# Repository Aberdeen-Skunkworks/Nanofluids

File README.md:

# Nanofluids

Project background:

Moore's Law is a well-known phenomenon that states that in highly dense integrated circuits (IC) the total number of transistors will approximately double every two years. Thermal management becomes unrealistic as the density of transistors with in the IC increase, thus a new challenge has appeared in heat transfer: cooling of nano-scale devices. A more efficient and compact design of heat exchangers is required for advanced nanoelectronics, and one way this can be achieved is through nanofluid technology. A very large enhancement of the thermal conductivity of a base fluid (i.e. water) can be achieved by the addition of highly conductive solid material in the form of nanoparticles. The mechanics of this enhancement have generally fallen into the classical/continuum bounds given by series and parallel resistances. These bounds are defined by two separate phases of the solid nanoparticles and the liquid medium and the arrangement of the nanoparticles with in the medium. But a small number of experimental result do not fall into these bounds such as helium and hydrogen gas mixtures or the theoretical hard sphere model, which instead exhibit conductivity enhancements above the parallel bounds and dehancement below the series bounds. This project is to explore this phenomena, both experimentally and theoretically, and to attempt to model its effects.

Project Objectives

• Review nanofluids and their history in thermal conductivity enhancement. This includes describing what models have already been used to approximate their behaviour and critically review their applicability.

•	Construct a Transient Heated Wire cell for the testing of liquid and gas mixture thermal conductivities and use this data to explore the anomalous heat transfer in nanofluids and gas mixtures which have similar dimensional properties to nanofluid systems.

• Perform molecular simulations of thermal conduction to confirm if transient effects in the thermal conductivity, possible at small time/length scales, dominate conduction. These simulations may be molecular dynamics simulations using DynamO, or coupled kinetic theory-hydrodynamics simulations using code developed by Craig Moir, a PhD student at Aberdeen

•	Explore new heat exchanger designs which incorporate any time-dependent anomalous phenomena

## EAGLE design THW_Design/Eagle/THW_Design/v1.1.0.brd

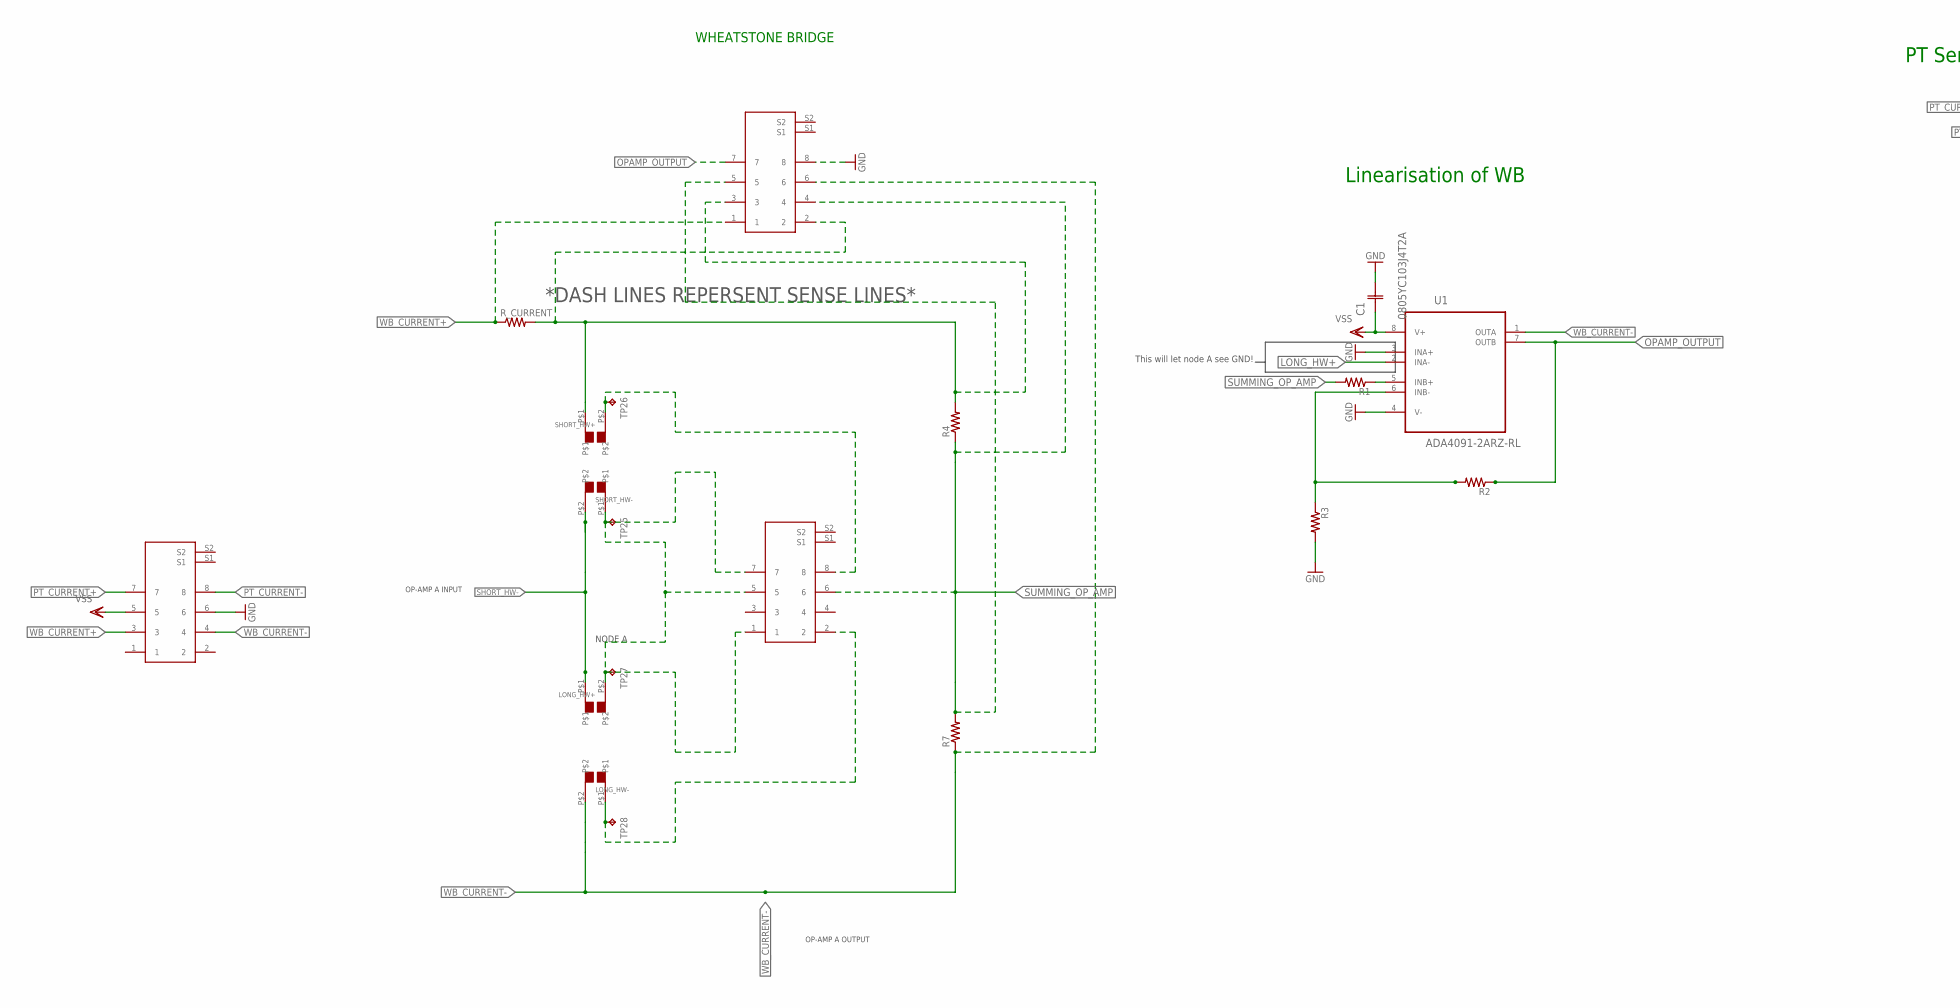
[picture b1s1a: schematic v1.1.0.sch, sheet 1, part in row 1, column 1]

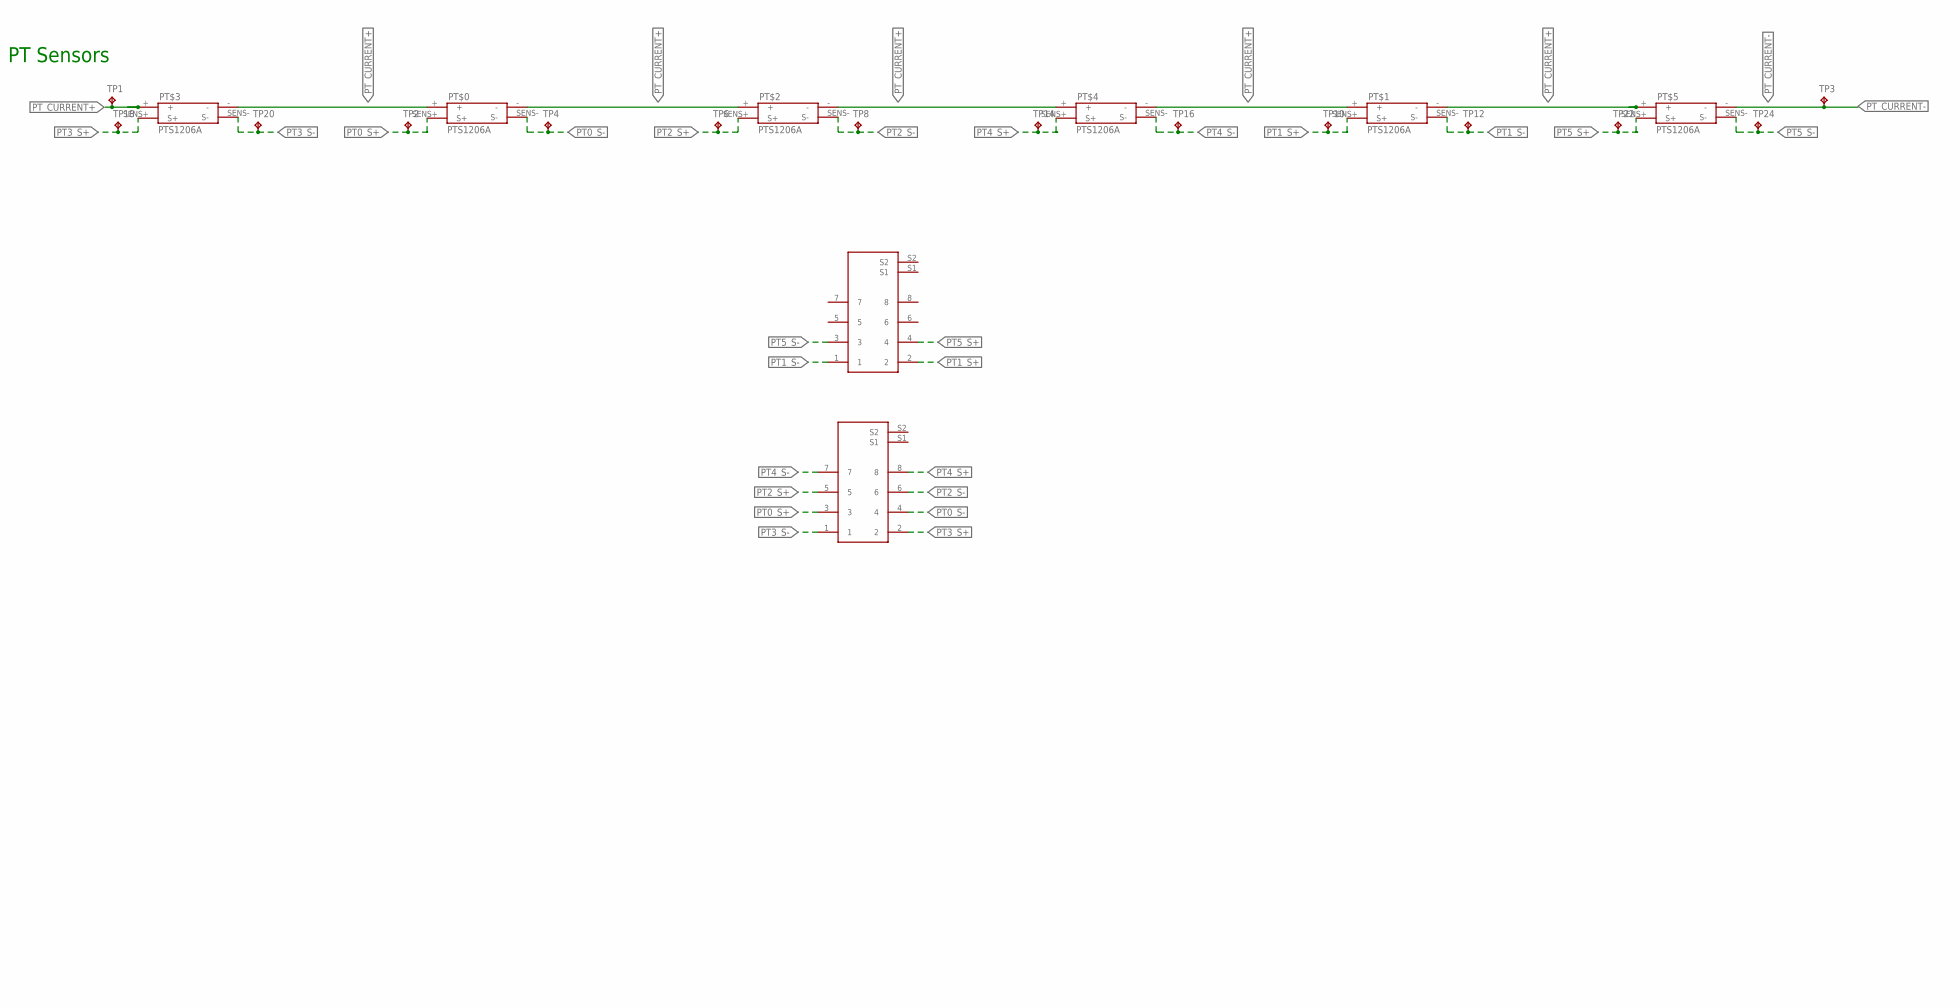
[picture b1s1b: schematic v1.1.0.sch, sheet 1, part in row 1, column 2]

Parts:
C1: 0805YC103J4T2A; CAPC2012X94N
LONG_HW+: WIREPOINT_1A; WIREPOINT
LONG_HW-: WIREPOINT_1A; WIREPOINT
POWER: RJ45_CONNECTOR; RJ45_CONNNECTOR
PT$0, PT$1, PT$2, PT$3, PT$4, PT$5: PTS1206A; CAPMP3216X166
PT_SENS1, PT_SENS2: RJ45_CONNECTOR; RJ45_CONNNECTOR
R1, R2, R3, R4, R7: R-US_M0805; M0805
R_CURRENT: R-US_M0805; M0805
SHORT_HW+: WIREPOINT_1A; WIREPOINT
SHORT_HW-: WIREPOINT_1A; WIREPOINT
TP1, TP2, TP3, TP4, TP6, TP8, TP10, TP12, TP14, TP16, TP18, TP20, TP22, TP24, TP25, TP26, TP27, TP28: TPTP10SQ; TP10SQ
U1: ADA4091-2ARZ-RL; SOIC127P600X175-8N
WB_SENS1, WB_SENS2: RJ45_CONNECTOR; RJ45_CONNNECTOR

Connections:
GND: C1.2 (C2), POWER.6, R3.2, U1.3 (INA+), U1.4 (V-), WB_SENS2.8
LONG_HW+: U1.2 (INA-)
LONG_HW_SENS-: LONG_HW-.P$1, TP28.TP, WB_SENS1.2
unnamed: R1.1, U1.5 (INB+)
unnamed: R2.2, R3.1, U1.6 (INB-)
OPAMP_OUTPUT: R2.1, U1.7 (OUTB), WB_SENS2.7
PT0_S+: PT$0.SENS+ (S+), PT_SENS2.3, TP2.TP
PT0_S-: PT$0.SENS- (S-), PT_SENS2.4, TP4.TP
PT1_S+: PT$1.SENS+ (S+), PT_SENS1.2, TP10.TP
PT1_S-: PT$1.SENS- (S-), PT_SENS1.1, TP12.TP
PT2_S+: PT$2.SENS+ (S+), PT_SENS2.5, TP6.TP
PT2_S-: PT$2.SENS- (S-), PT_SENS2.6, TP8.TP
PT3_S+: PT$3.SENS+ (S+), PT_SENS2.2, TP18.TP
PT3_S-: PT$3.SENS- (S-), PT_SENS2.1, TP20.TP
PT4_S+: PT$4.SENS+ (S+), PT_SENS2.8, TP14.TP
PT4_S-: PT$4.SENS- (S-), PT_SENS2.7, TP16.TP
PT5_S+: PT$5.SENS+ (S+), PT_SENS1.4, TP22.TP
PT5_S-: PT$5.SENS- (S-), PT_SENS1.3, TP24.TP
PT_CURRENT+: POWER.7, PT$0.+, PT$0.-, PT$1.+, PT$1.-, PT$2.+, PT$2.-, PT$3.+, PT$3.-, PT$4.+, PT$4.-, PT$5.+, TP1.TP
PT_CURRENT-: POWER.8, PT$5.-, TP3.TP
SHORT_HW+: R4.2, R_CURRENT.2, SHORT_HW+.P$1, WB_SENS2.2, WB_SENS2.3
SHORT_HW-: LONG_HW+.P$1, SHORT_HW-.P$2
SHORT_HW_SENS+: SHORT_HW+.P$2, TP26.TP, WB_SENS1.8
SHORT_HW_SENS-: LONG_HW+.P$2, SHORT_HW-.P$1, TP25.TP, TP27.TP, WB_SENS1.1, WB_SENS1.5, WB_SENS1.7
SUMMING_OP_AMP: R1.2, R4.1, R7.2, WB_SENS1.6, WB_SENS2.4, WB_SENS2.5
VSS: C1.1 (C1), POWER.5, U1.8 (V+)
WB_CURRENT+: POWER.3, R_CURRENT.1, WB_SENS2.1
WB_CURRENT-: LONG_HW-.P$2, POWER.4, R7.1, U1.1 (OUTA), WB_SENS2.6

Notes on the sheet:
WHEATSTONE BRIDGE
Linearisation of WB
PT Sensors
OP-AMP A INPUT
OP-AMP A OUTPUT
NODE A
This will let node A see GND!
*DASH LINES REPERSENT SENSE LINES*

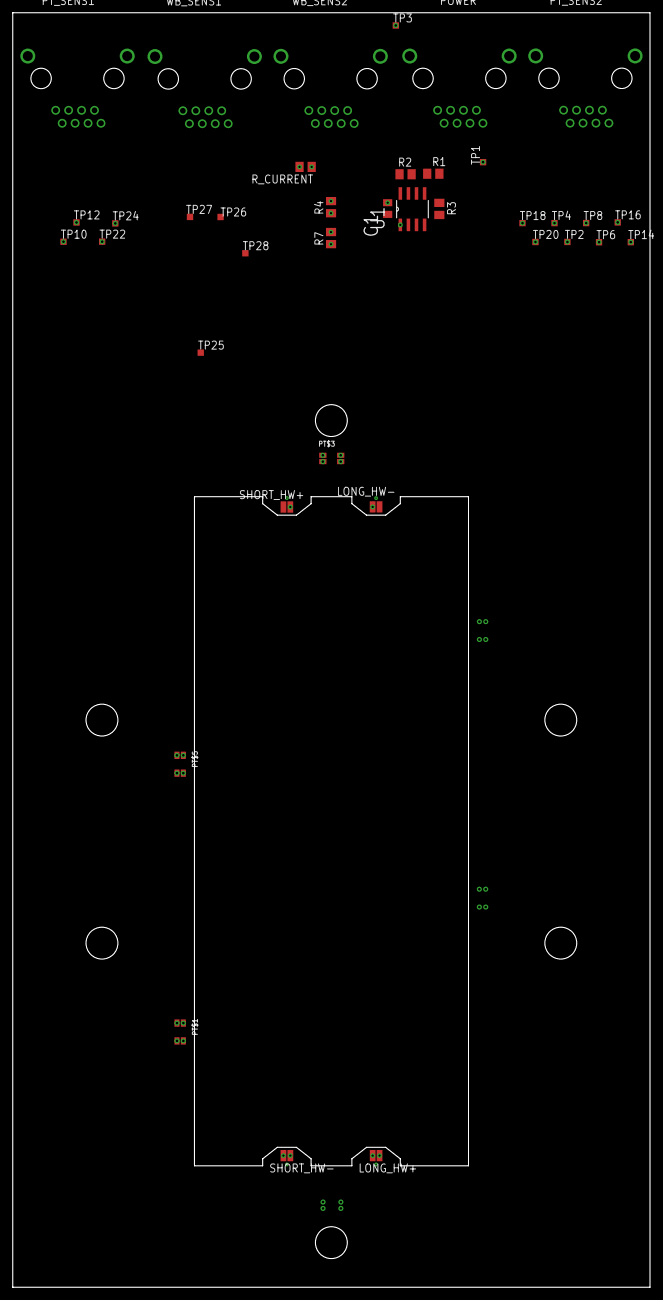
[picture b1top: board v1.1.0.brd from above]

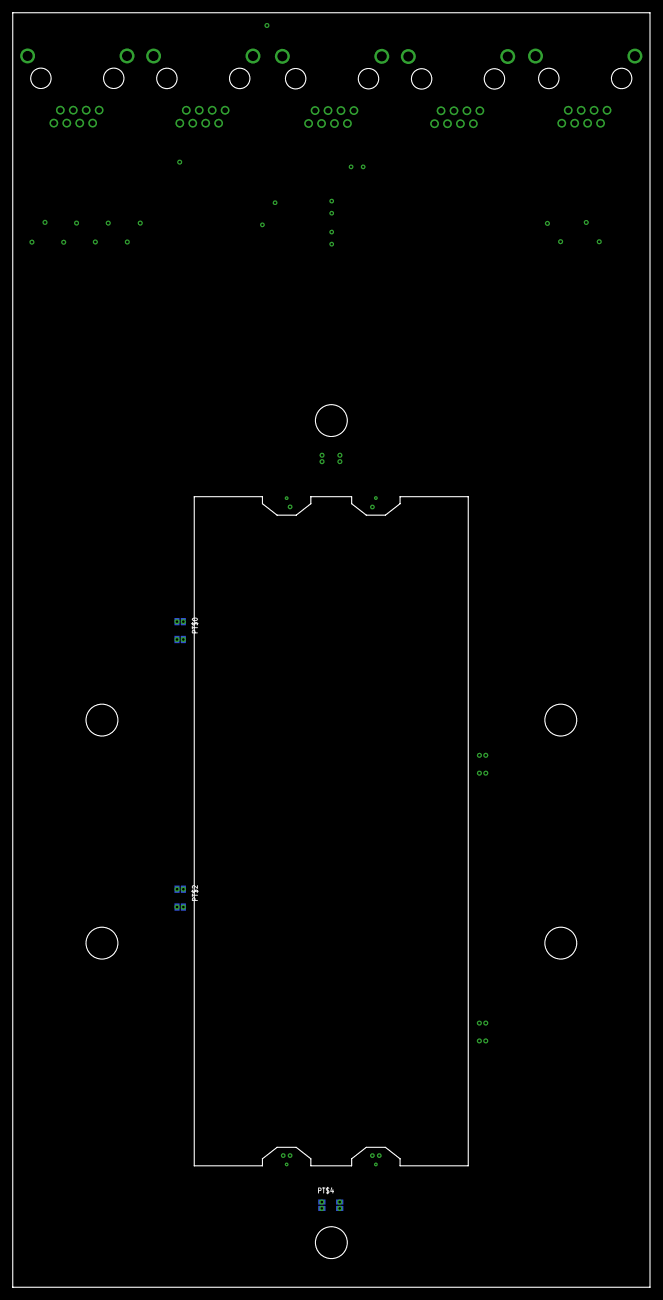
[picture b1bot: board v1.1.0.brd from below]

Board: 4 copper layers, 100.0 x 200.0 mm, 41 parts (3 on the bottom side), 27 nets.

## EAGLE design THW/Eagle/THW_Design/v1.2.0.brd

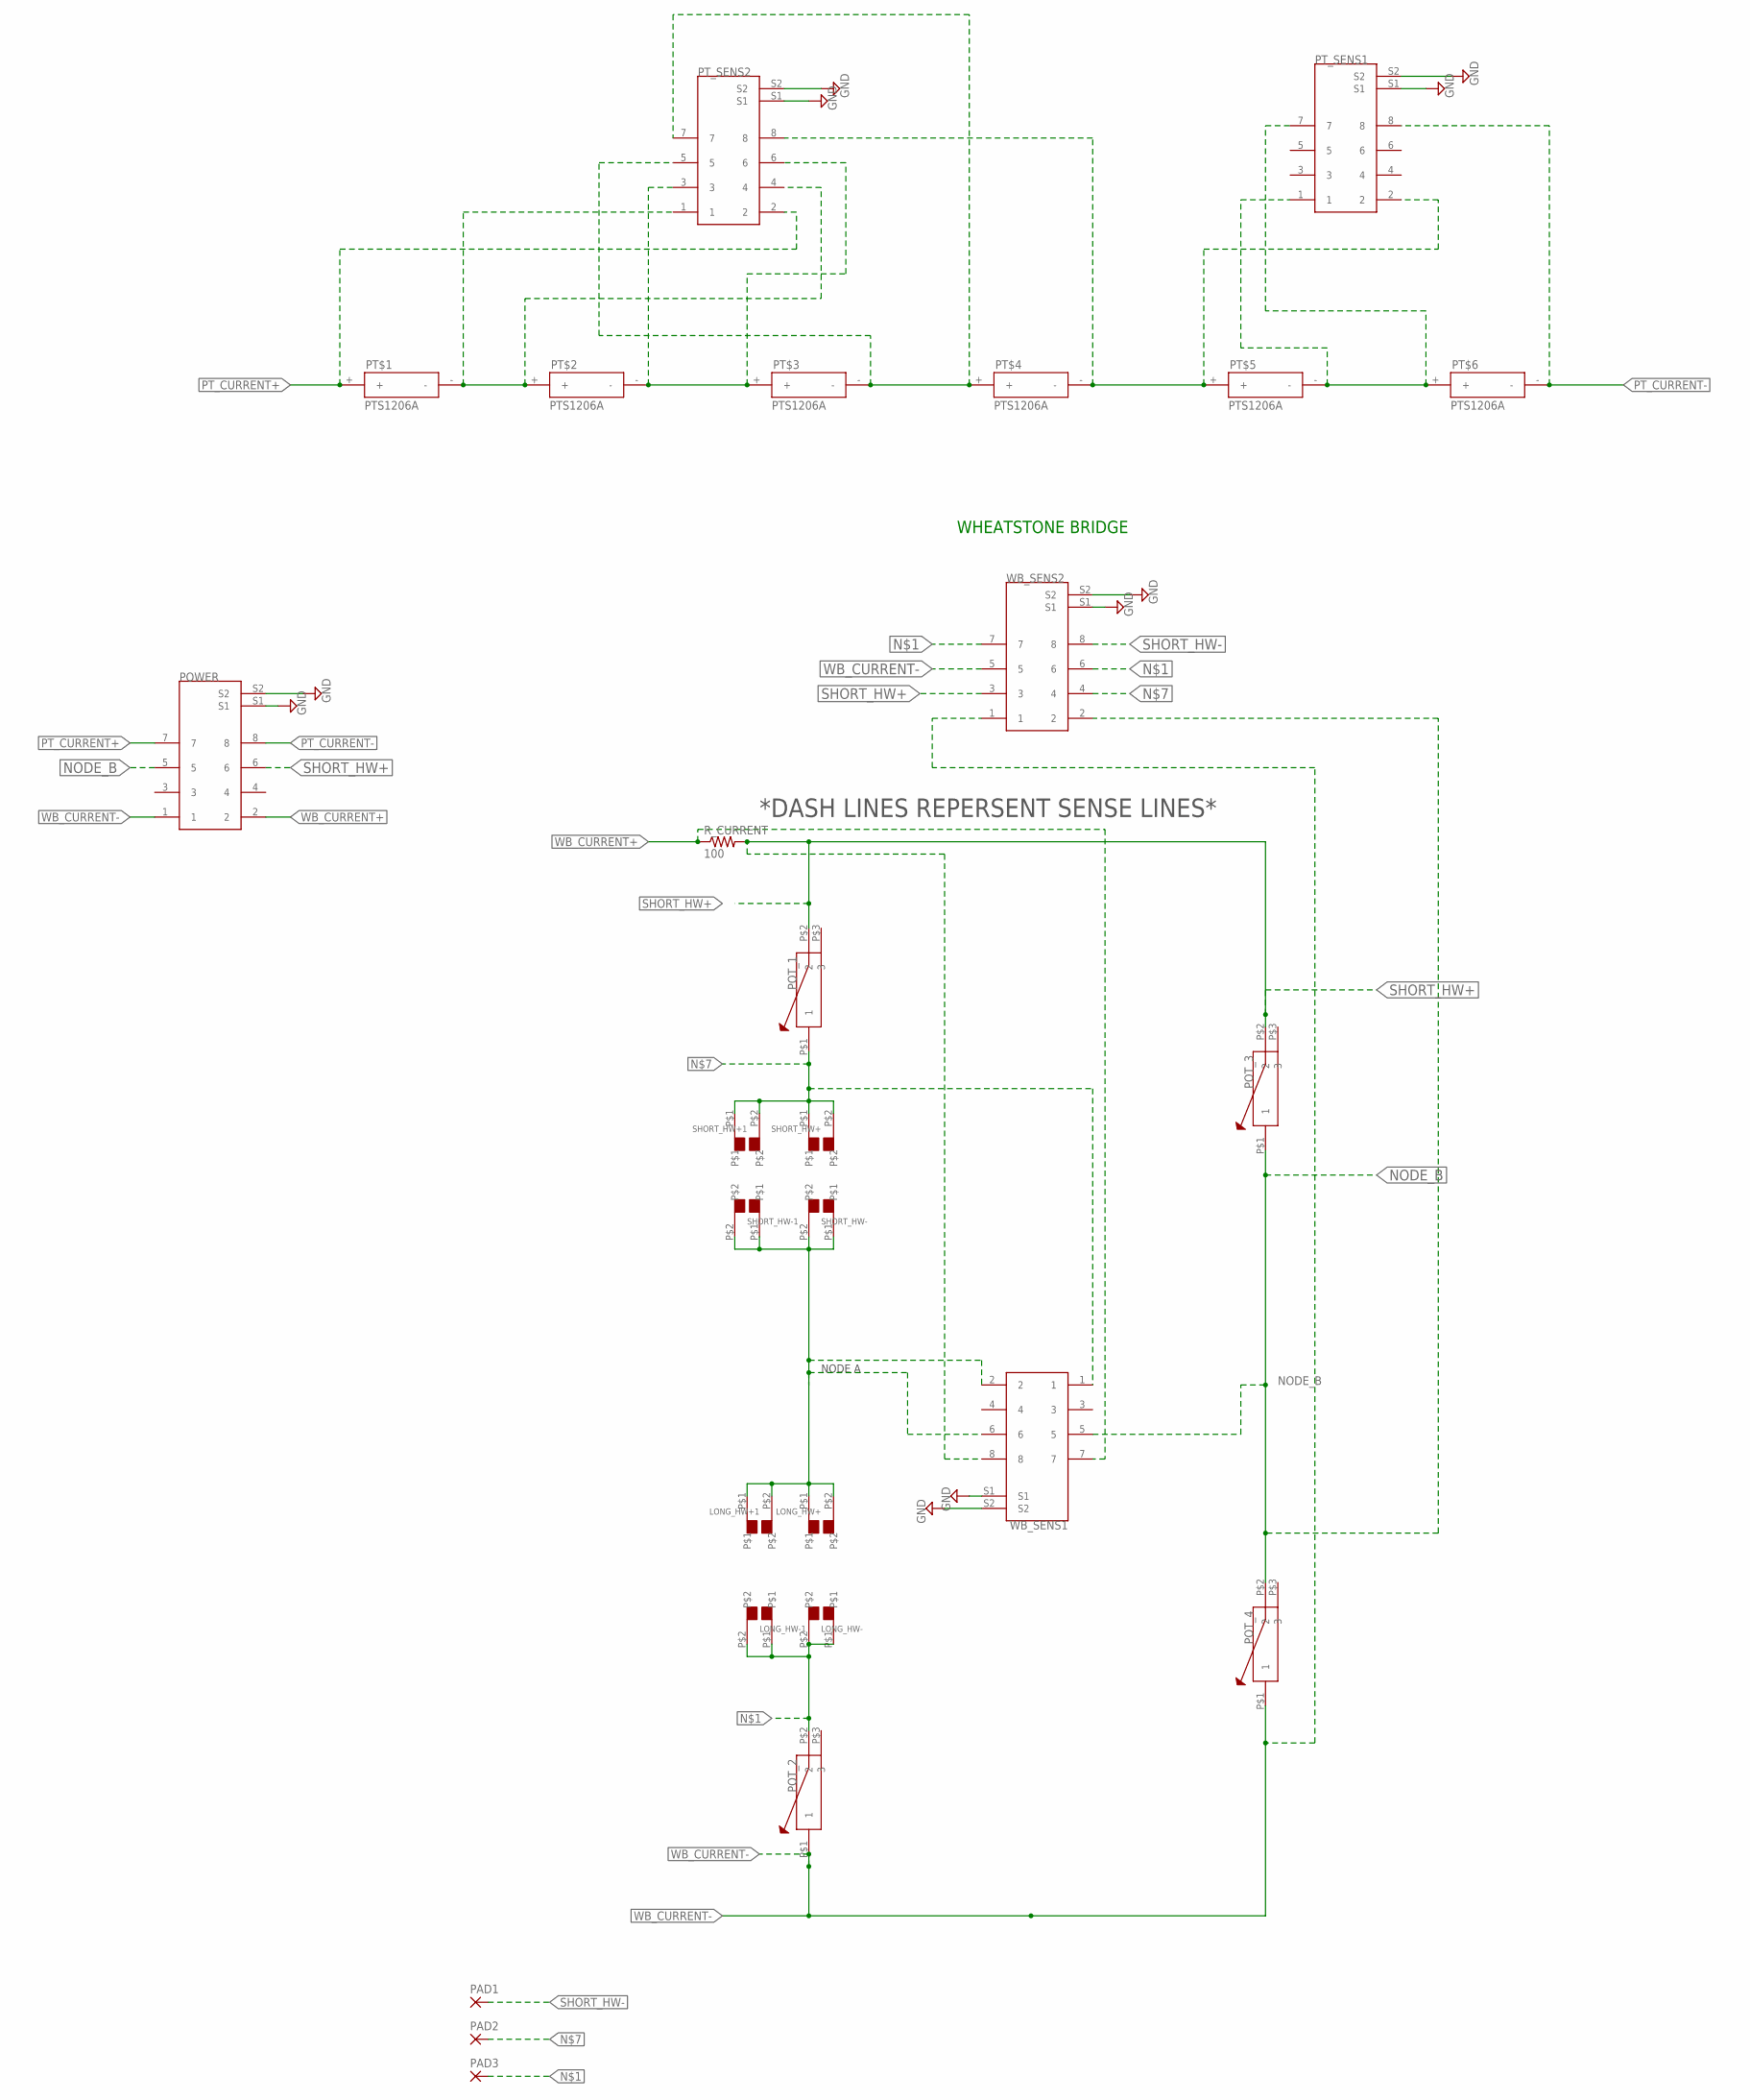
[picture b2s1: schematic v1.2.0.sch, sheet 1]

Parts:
LONG_HW+, LONG_HW+1: WIREPOINT_1A; WIREPOINT
LONG_HW-, LONG_HW-1: WIREPOINT_1A; WIREPOINT
PAD1, PAD2, PAD3: 2,15/1,0
POT_1, POT_2, POT_3, POT_4: 67WR200LFR$1; 67WR200LF
POWER: RJ45_CONNECTOR; RJ45_CONNNECTOR
PT$1, PT$2, PT$3, PT$4, PT$5, PT$6: PTS1206A; CAPMP3216X166
PT_SENS1, PT_SENS2: RJ45_CONNECTOR; RJ45_CONNNECTOR
R_CURRENT: 100; M0805
SHORT_HW+, SHORT_HW+1: WIREPOINT_1A; WIREPOINT
SHORT_HW-, SHORT_HW-1: WIREPOINT_1A; WIREPOINT
WB_SENS1, WB_SENS2: RJ45_CONNECTOR; RJ45_CONNNECTOR

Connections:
GND: POWER.S1, POWER.S2, PT_SENS1.S1, PT_SENS1.S2, PT_SENS2.S1, PT_SENS2.S2, WB_SENS1.S1, WB_SENS1.S2, WB_SENS2.S1, WB_SENS2.S2
unnamed: LONG_HW-.P$1, LONG_HW-.P$2, LONG_HW-1.P$1, LONG_HW-1.P$2, PAD3.1, POT_2.P$2 (2), WB_SENS2.6, WB_SENS2.7
unnamed: PT$2.-, PT$3.+, PT_SENS2.3, PT_SENS2.6
unnamed: PT$3.-, PT$4.+, PT_SENS2.5, PT_SENS2.7
unnamed: PT$4.-, PT$5.+, PT_SENS1.2, PT_SENS2.8
unnamed: PT$5.-, PT$6.+, PT_SENS1.1, PT_SENS1.7
unnamed: PAD2.1, POT_1.P$1 (1), SHORT_HW+.P$1, SHORT_HW+.P$2, SHORT_HW+1.P$1, SHORT_HW+1.P$2, WB_SENS1.1, WB_SENS2.4
unnamed: PT$1.-, PT$2.+, PT_SENS2.1, PT_SENS2.4
NODE_B: POT_3.P$1 (1), POT_4.P$2 (2), POWER.5, WB_SENS1.5, WB_SENS2.2
PT_CURRENT+: POWER.7, PT$1.+, PT_SENS2.2
PT_CURRENT-: POWER.8, PT$6.-, PT_SENS1.8
SHORT_HW+: POT_1.P$2 (2), POT_3.P$2 (2), POWER.6, R_CURRENT.2, WB_SENS1.8, WB_SENS2.3
SHORT_HW-: LONG_HW+.P$1, LONG_HW+.P$2, LONG_HW+1.P$1, LONG_HW+1.P$2, PAD1.1, SHORT_HW-.P$1, SHORT_HW-.P$2, SHORT_HW-1.P$1, SHORT_HW-1.P$2, WB_SENS1.2, WB_SENS1.6, WB_SENS2.8
WB_CURRENT+: POWER.2, R_CURRENT.1, WB_SENS1.7
WB_CURRENT-: POT_2.P$1 (1), POT_4.P$1 (1), POWER.1, WB_SENS2.1, WB_SENS2.5

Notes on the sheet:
WHEATSTONE BRIDGE
NODE A
*DASH LINES REPERSENT SENSE LINES*

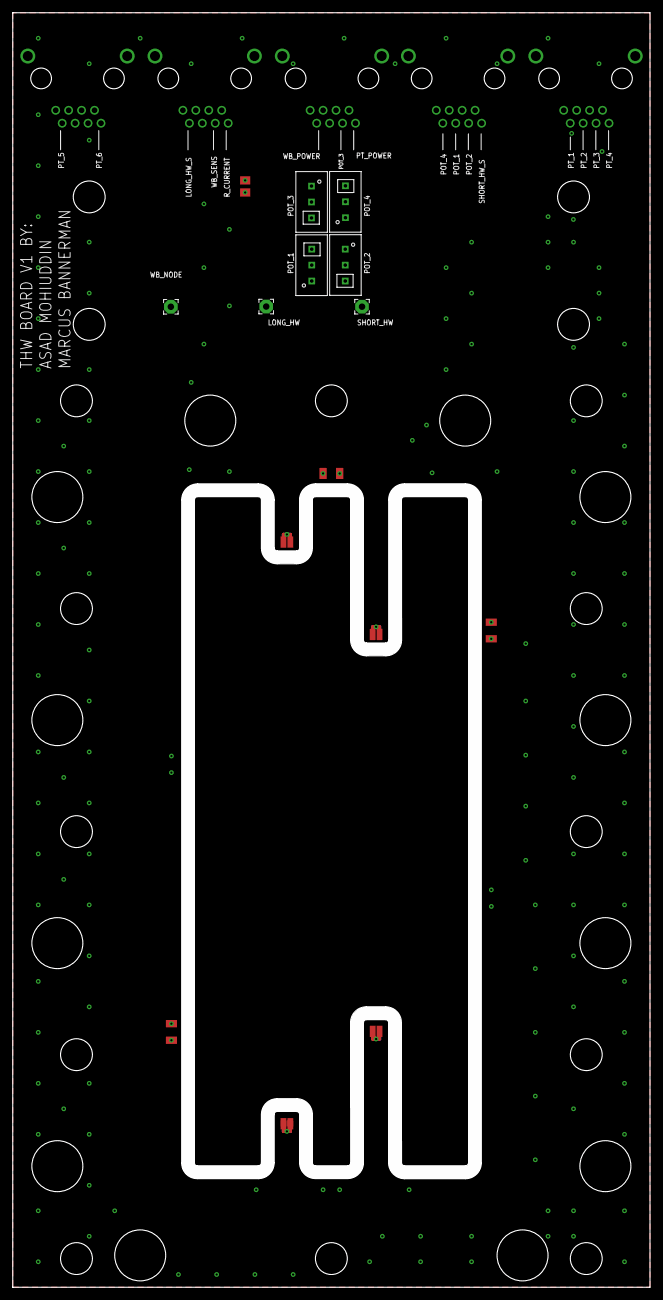
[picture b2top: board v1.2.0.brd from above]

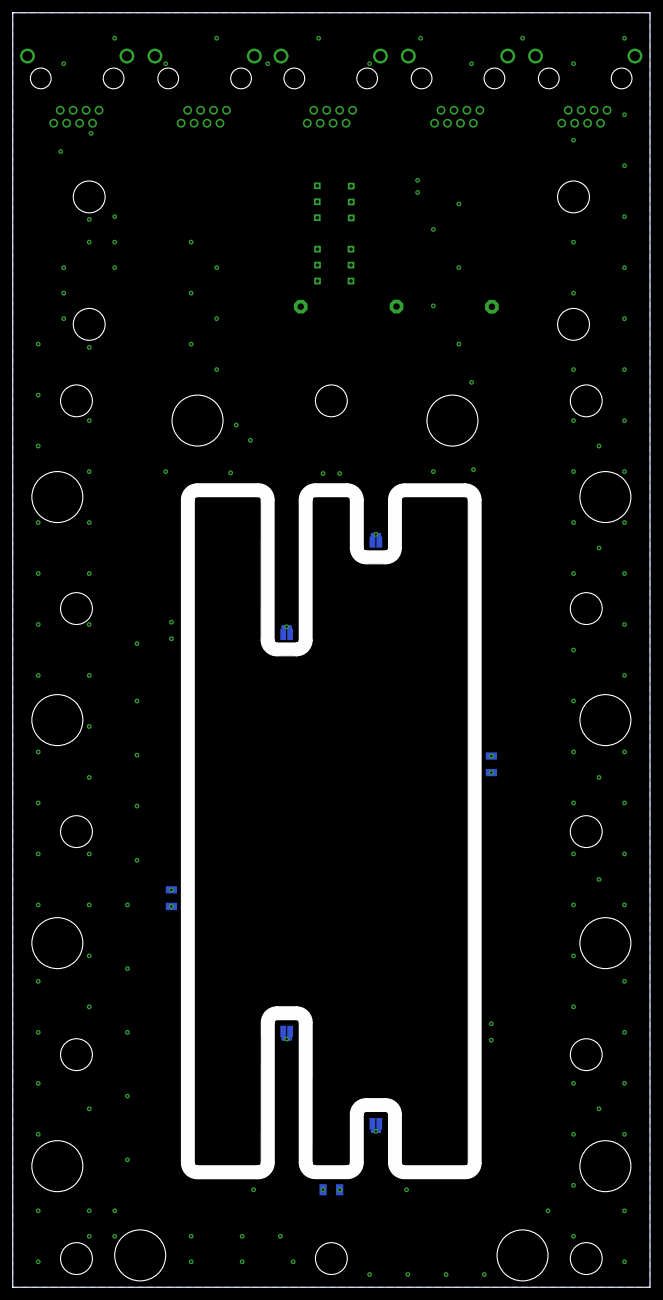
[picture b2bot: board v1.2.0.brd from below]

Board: 4 copper layers, 100.0 x 200.0 mm, 28 parts (7 on the bottom side), 15 nets.

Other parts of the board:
U$1: AD_LOGO

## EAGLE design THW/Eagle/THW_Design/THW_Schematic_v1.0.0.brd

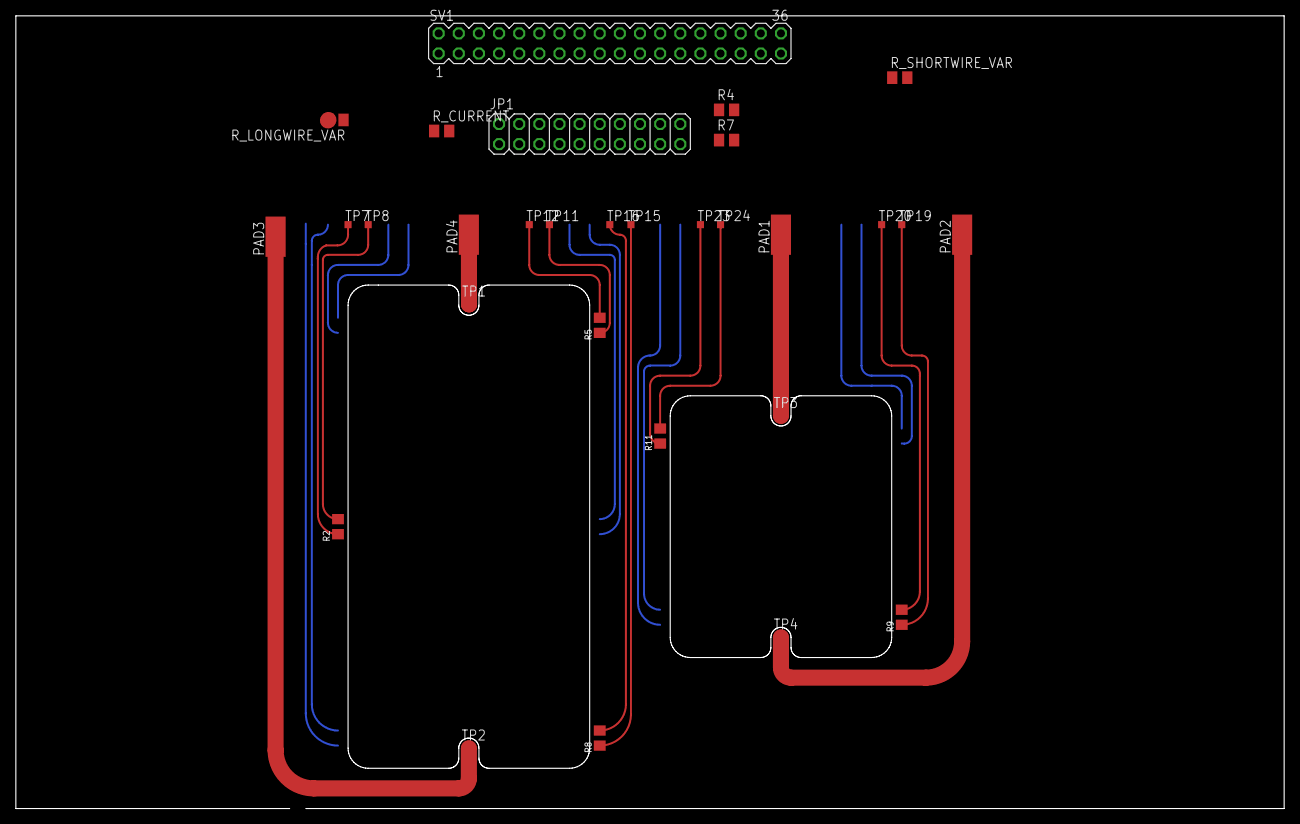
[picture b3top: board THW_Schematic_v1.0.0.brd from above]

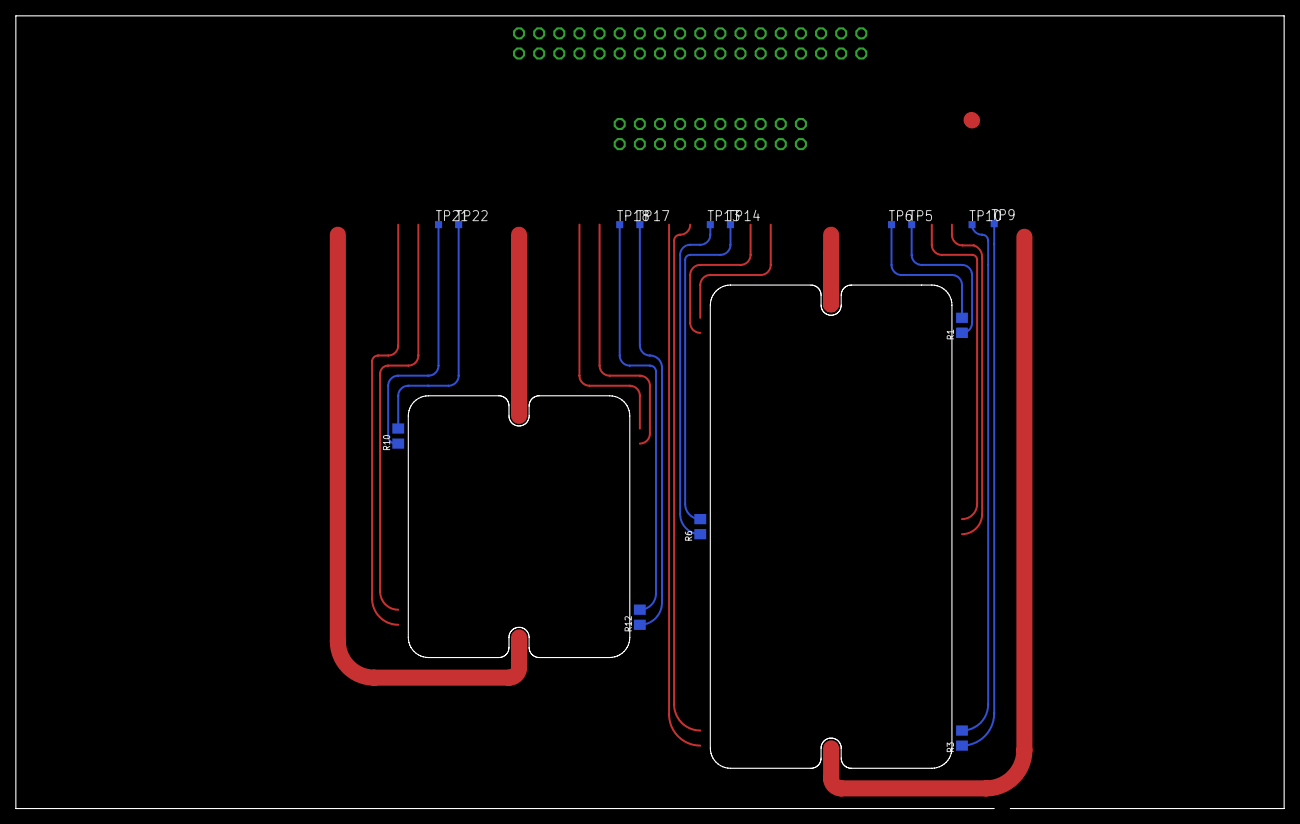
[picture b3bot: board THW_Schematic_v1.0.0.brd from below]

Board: 3 copper layers, 160.0 x 100.0 mm, 45 parts (15 on the bottom side), 27 nets.

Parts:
JP1: 2X10
PAD1, PAD2, PAD3, PAD4: SMD2,54-5,08
R1, R2, R3, R5, R6, R8, R9, R10, R11, R12: PTS080501B500RP100; RESC2012X60
R4, R7: M0805
R_CURRENT: M0805
R_LONGWIRE_VAR: M0805
R_SHORTWIRE_VAR: M0805
SV1: MA18-2
TP1, TP2, TP3, TP4: PTR1TP20R; TP20R
TP5, TP6, TP7, TP8, TP9, TP10, TP11, TP12, TP13, TP14, TP15, TP16, TP17, TP18, TP19, TP20, TP21, TP22, TP23, TP24: TPSQTP09SQ; TP09SQ

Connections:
GND: R7.1, R_SHORTWIRE_VAR.2, SV1.25, SV1.33
LONG_HW+: PAD4.1, R4.2, R_CURRENT.2, SV1.1, SV1.30, TP1.TP
LONG_HW-: PAD3.1, R_LONGWIRE_VAR.2, SV1.2, SV1.28, TP2.TP
unnamed: R4.1, R7.2
SHORT_HW+: PAD1.1, R_LONGWIRE_VAR.1, SV1.27, SV1.35, TP3.TP
SHORT_HW-: PAD2.1, R_SHORTWIRE_VAR.1, SV1.26, SV1.36, TP4.TP
T_S1+: JP1.1, R1.1, TP5.TP
T_S1-: JP1.2, R1.2, TP6.TP
T_S2+: JP1.3, R2.1, TP7.TP
T_S2-: JP1.4, R2.2, TP8.TP
T_S3+: JP1.5, R3.1, TP9.TP
T_S3-: JP1.6, R3.2, TP10.TP
T_S4+: JP1.7, R5.1, TP11.TP
T_S4-: JP1.8, R5.2, TP12.TP
T_S5+: JP1.9, R6.1, TP13.TP
T_S5-: JP1.10, R6.2, TP14.TP
T_S6+: JP1.11, R8.1, TP15.TP
T_S6-: JP1.12, R8.2, TP16.TP
T_S7+: R12.1, TP17.TP
T_S7-: JP1.14, R12.2, TP18.TP
T_S8+: JP1.17, R9.1, TP19.TP
T_S8-: JP1.18, R9.2, TP20.TP
T_S9+: JP1.19, R10.1, TP21.TP
T_S9-: JP1.20, R10.2, TP22.TP
T_S10+: JP1.15, R11.1, TP23.TP
T_S10-: JP1.16, R11.2, TP24.TP
VSS: R_CURRENT.1, SV1.29, SV1.34

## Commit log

2018-09-27 Readme
2018-09-28 added PCB v1.0.0
2018-10-02 eagle
2018-10-02 changed version
2018-10-02 resistance on traces
2018-10-11 new version
2018-10-12 adding one current source to PT sensors
2018-10-15 routing
2018-10-17 new traces
2018-10-17 Some polygon work for Asad
2018-10-17 finish routing pt sensors tomorrow
2018-10-18 added the cool logo
2018-10-19 Marcus changes at office
2018-10-20 stitching
2018-10-21 peeled back solder mask for cell contacts
2018-10-22 Minor changes to design and logo package
2018-10-26 moving to PC, eagle getting laggy
2018-10-26 fixed cell window
2018-10-27 updated shopping list
2018-10-27 V1 THW DONE :)!
2018-10-29 4-wire sense
2018-11-02 push
2018-11-02 PUSHHH
2018-11-03 added Maxwell Plot
2018-11-03 added silkscreens where needed, stiching via's need to be worked
2018-11-03 stiching via
2018-11-03 More work
2018-11-03 fix sheild pin
2018-11-03 removed tNames
2018-11-03 Updated the board
2018-11-03 RJ45 POT
2018-11-03 Fixed thermals on bottom sheild, and the wire supports
2018-11-03 updated rj45 dimensions
2018-11-03 More fixes
2018-11-13 fusiom 360 ani
2018-11-14 modelling THW
2018-11-14 more work on modelling THW
2018-11-17 thw ideal corrections
2018-11-18 Correction factors
2019-05-13 new commit
2019-05-13 deleting files
2019-05-17 Fixed UI, improved experiment speed, uses MOSFETS
2019-05-17 Removing temporary files, also working on single wire script
2019-05-21 Started on the new controller class
2019-05-21 Figured out remote resetting of the rack and better error checking
2019-05-21 More work on the new class and checking
2019-05-22 Trying to get the relay working, but this commit has broken RTD probe reads
2019-05-23 RTD now working again, also added checking the current sense resistor resistance
2019-05-23 Added instrument classes to provide better error detection
2019-05-24 Added more error checking, and now working on the relay mux class
2019-05-25 More work, gotten the relay mux to be a lot cleaner/extendable
2019-05-27 Have added data logging for calibration
2019-06-05 Fixed an issue with the new reset_rack and error checking
2019-06-05 Now performing transient heated wire tests
2019-06-05 Now the THW test collects 6k samples at 13kHz, with accurate current metering
2019-06-06 Fully working setup! Now just need to interpret I hope!
2019-06-06 Forgotten file for last commit
2019-06-13 Working calibration on the wires and some single wire tests
2019-06-14 Now have multiple q value experiments
2019-07-31 Added the new THW control script
2019-08-01 Some updates to THW.py
2019-08-01 REimplementation of yesterdays changes
2020-01-31 Working with the K194, need to get cal working etc
2020-02-04 System now measures both lines, reads thermostats etc.
2020-02-14 Update THW66311B.ipynb
    Added second PT100
